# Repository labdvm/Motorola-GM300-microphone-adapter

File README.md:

# Motorola-GM300-microphone-adapter
Motorola GM300 microphone adapter to other radios
I hope this will work :-)
Z32IT

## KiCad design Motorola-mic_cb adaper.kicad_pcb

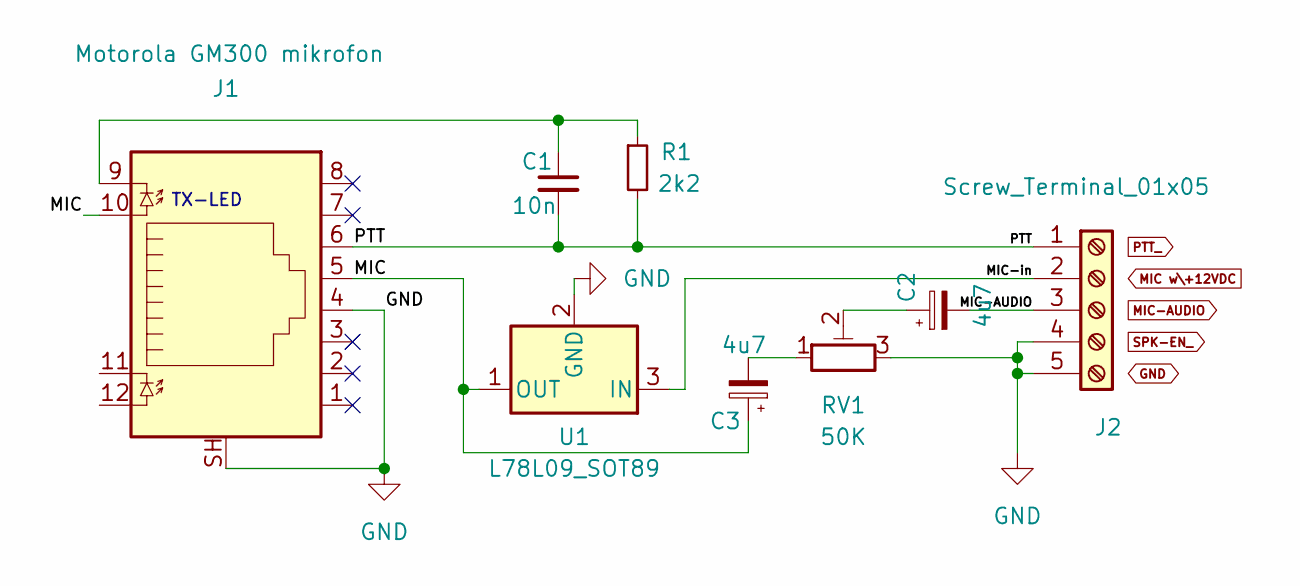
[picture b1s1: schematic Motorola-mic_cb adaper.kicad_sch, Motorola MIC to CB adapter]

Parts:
C1: 10n; C_0805_2012Metric
C2, C3: 4u7; CP_EIA-3528-12_Kemet-T
J1: Motorola GM300 mikrofon; RJ45_Amphenol_RJHSE538X
J2: Screw_Terminal_01x05; TerminalBlock_MaiXu_MX126-5.0-05P_1x05_P5.00mm
R1: 2k2; R_0805_2012Metric
RV1: 50K; Potentiometer_Piher_PT-10-V10_Vertical
U1: L78L09_SOT89; SOT-89-3

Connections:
/MIC-in: J2.2, U1.3 (IN)
/PTT: C1.2, J1.6, J2.1, R1.2
GND: J1.4, J1.SH, J2.4, J2.5, RV1.3, U1.2 (GND)
MIC: C3.1, J1.5, J1.10, U1.1 (OUT)
MIC-AUDIO: C2.2, J2.3
unnamed: C1.1, J1.9, R1.1
unnamed: C2.1, RV1.2
unnamed: C3.2, RV1.1

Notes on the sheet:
TX-LED

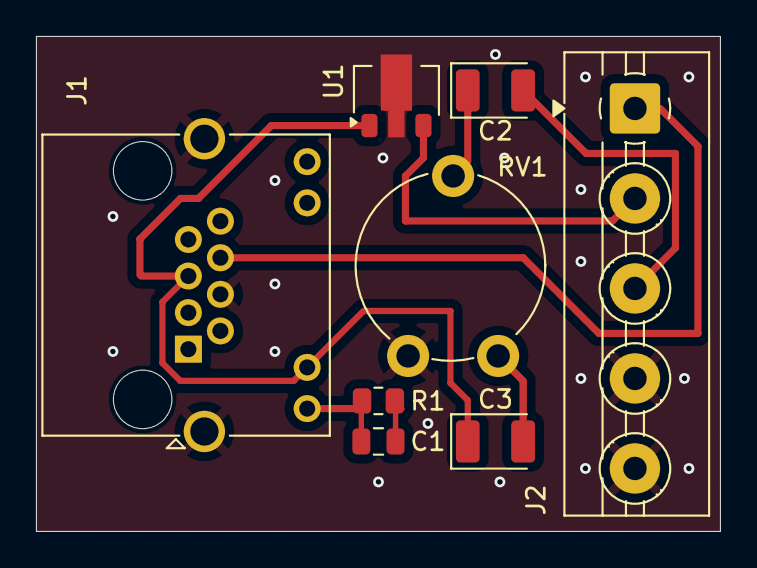
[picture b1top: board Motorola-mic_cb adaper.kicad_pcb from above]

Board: 2 copper layers, 38.0 x 27.5 mm, 8 parts (0 on the bottom side), 8 nets.

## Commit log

2026-01-16 Fix typo in README.md
